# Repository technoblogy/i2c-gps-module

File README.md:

# I2C GPS Module
An I2C GPS module based on an ATtiny841 and a GTPA010 GPS module. See <http://www.technoblogy.com/show?2C86>.

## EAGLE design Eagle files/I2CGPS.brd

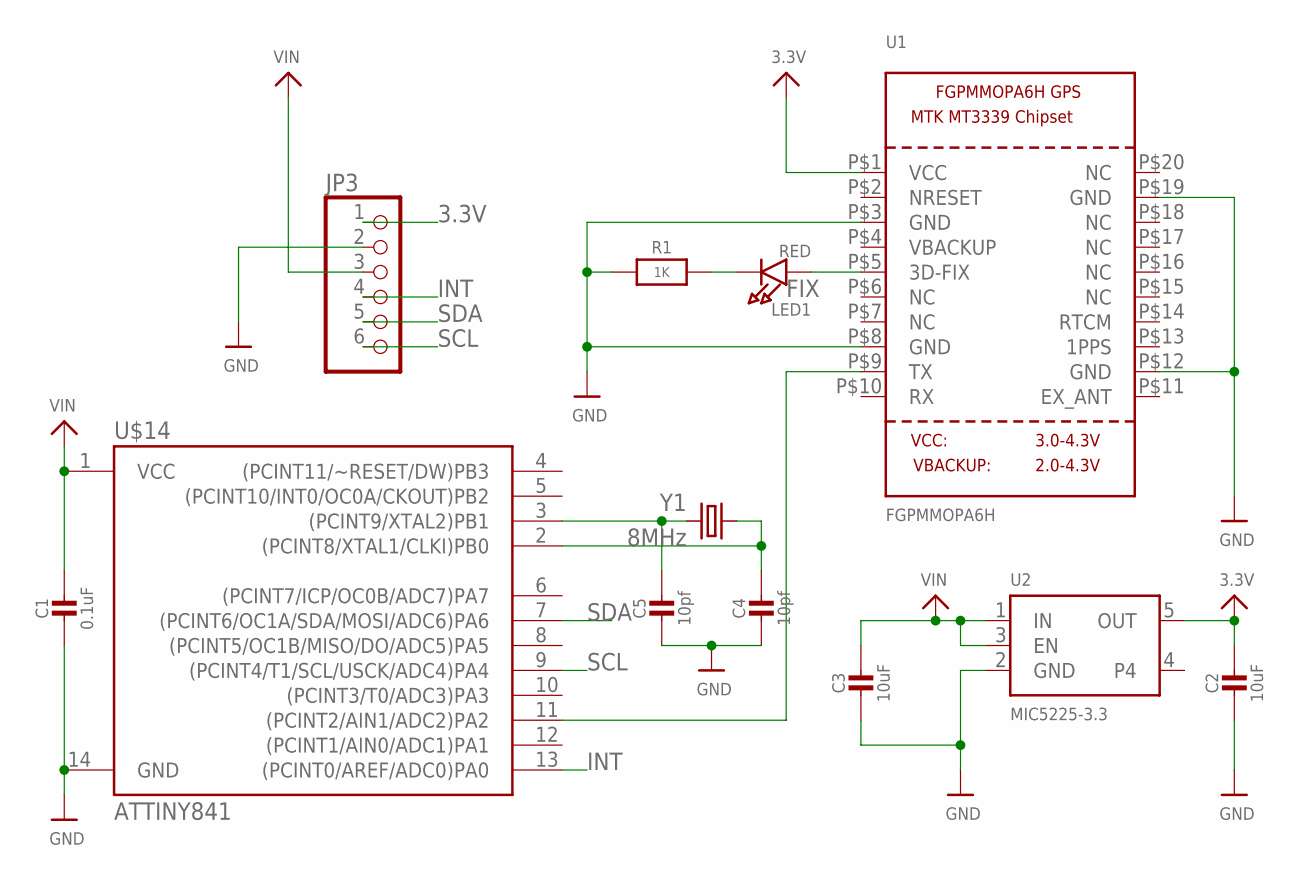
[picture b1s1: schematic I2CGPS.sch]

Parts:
C1: 0.1uF; 0805-NO
C2, C3: 10uF; 0805-NO
C4, C5: 10pf; 0805-NO
JP3: PINHD-1X6CB; 1X06-CLEANBIG
LED1: RED; CHIPLED_0805_NOOUTLINE
R1: 1K; 0805-NO
U1: FGPMMOPA6H
U2: MIC5225-3.3; SOT23-5
U$14: ATTINY841; SO14
Y1: 8MHz; CRYSTAL-SMD-5X3

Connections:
3.3V: C2.1, JP3.1, U1.P$1 (VCC), U2.5 (OUT)
FIX: LED1.A, U1.P$5 (3D-FIX)
GND: C1.2, C2.2, C3.2, C4.2, C5.2, JP3.2, R1.1, U1.P$3 (GND), U1.P$8 (GND), U1.P$12 (GND), U1.P$19 (GND), U2.2 (GND), U$14.14 (GND)
INT: JP3.4, U$14.13 ((PCINT0/AREF/ADC0)PA0)
unnamed: C4.1, U$14.2 ((PCINT8/XTAL1/CLKI)PB0), Y1.1
unnamed: LED1.C, R1.2
unnamed: C5.1, U$14.3 ((PCINT9/XTAL2)PB1), Y1.3 (2)
SCL: JP3.6, U$14.9 ((PCINT4/T1/SCL/USCK/ADC4)PA4)
SDA: JP3.5, U$14.7 ((PCINT6/OC1A/SDA/MOSI/ADC6)PA6)
TX: U1.P$9 (TX), U$14.11 ((PCINT2/AIN1/ADC2)PA2)
VIN: C1.1, C3.1, JP3.3, U2.1 (IN), U2.3 (EN), U$14.1 (VCC)

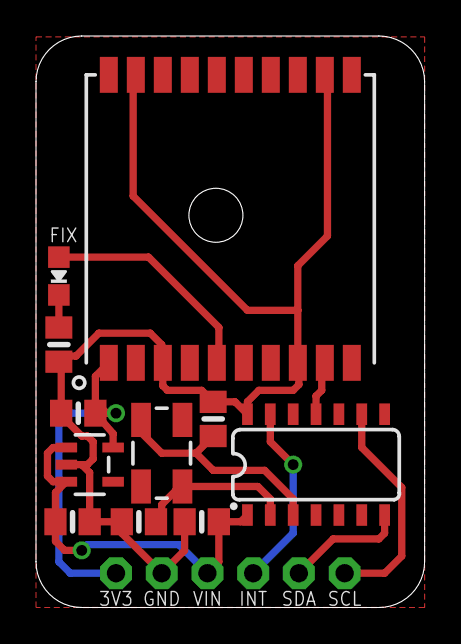
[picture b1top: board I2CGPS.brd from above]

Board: 2 copper layers, 21.6 x 31.8 mm, 12 parts (0 on the bottom side), 11 nets.

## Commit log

2018-11-15 Version 1 - 27th September 2018
2018-11-15 Version 1 - 15th November 2018

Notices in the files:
parts and their libraries:
SparkFun-DigitalIC: Licensing: Creative Commons ShareAlike 4.0 International - https://creativecommons.org/licenses/by-sa/4.0
